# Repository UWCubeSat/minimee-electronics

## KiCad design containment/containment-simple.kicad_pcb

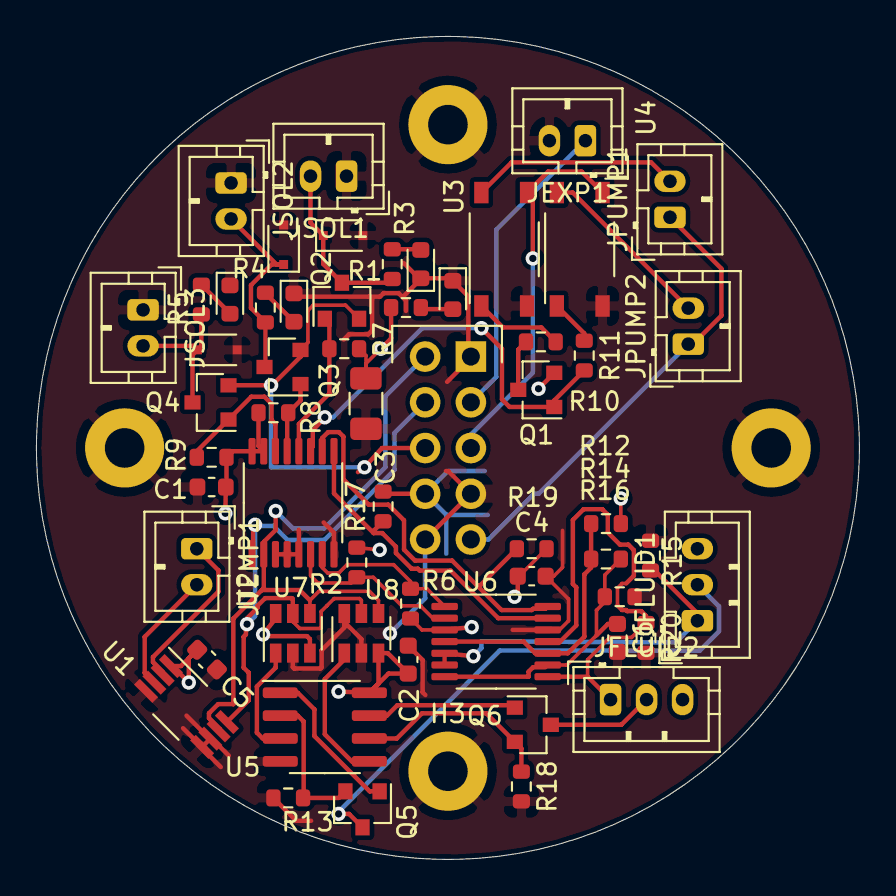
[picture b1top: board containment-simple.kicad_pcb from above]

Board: 2 copper layers, 45.7 x 45.7 mm, 61 parts (1 on the bottom side), 42 nets.

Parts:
C1, C2, C4, C5, C6: .1uF; C_0603_1608Metric
C3: 10uF; C_1206_3216Metric
D1, D5, D7, D9: LED; LED_0603_1608Metric
D4, D6, D8: D; D_SOD-323F
H1, H2, H3, H4: MountingHole_Pad; MountingHole_2-56_ExtraClearance
J1: Conn_02x05_Odd_Even; PinHeader_2x05_P2.54mm_Vertical
JEXP1: Conn_01x02; JST_PH_B2B-PH-K_1x02_P2.00mm_Vertical
JFLUID1, JFLUID2: Conn_01x03; JST_PH_B3B-PH-K_1x03_P2.00mm_Vertical
JPUMP1, JPUMP2: Conn_01x02; JST_PH_B2B-PH-K_1x02_P2.00mm_Vertical
JSOL1, JSOL2, JSOL3: Conn_01x02; JST_PH_B2B-PH-K_1x02_P2.00mm_Vertical
JTEMP1: Conn_01x02; JST_PH_B2B-PH-K_1x02_P2.00mm_Vertical
Q1, Q2, Q3, Q4: BSS84; SOT-23
Q5, Q6: BC846; SOT-23
R1, R3, R4, R5: 1k; R_0603_1608Metric
R2, R6, R7, R8, R9, R12, R14, R15, R16, R17, R19, R20: 10k; R_0603_1608Metric
R10, R11: 470; R_0603_1608Metric
R13, R18: 50; R_0603_1608Metric
U1: TMP411; VSSOP-8_3.0x3.0mm_P0.65mm
U2: PCA9557; TSSOP-16_4.4x5mm_P0.65mm
U3, U4: TLP175A; MFSOP6-4_4.4x3.6mm_P1.27mm
U5: LM358; SOIC-8_3.9x4.9mm_P1.27mm
U6: LM339; TSSOP-14_4.4x5mm_P0.65mm
U7, U8: MCP4725xxx-xCH; SOT-23-6

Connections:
+5V: C1.1, C2.1, C3.1, C4.1, C5.1, J1.8, JFLUID1.3, JFLUID2.3, Q1.2, R1.1, R2.1, R6.1, R7.1, R8.1, R9.1, R12.1, R17.1, R19.1, U1.1, U2.15, U2.16, U5.8, U6.3, U7.3, U7.6, U8.3
+12V: J1.6, Q2.2, Q3.2, Q4.2
/Fluid Sensors/1_3rds: C6.1, R14.2, R16.1, U6.7, U6.9
/Fluid Sensors/2_3rds: R12.2, R14.1, U6.4, U6.10
/HV+: J1.9, JPUMP1.1, JPUMP2.1
/HV-: J1.5, U3.4, U4.4
/experiment: J1.3, JEXP1.1
/p0: R2.2, U2.6, U6.2
/p1: R6.2, U2.7, U6.1
/p2: R17.2, U2.9, U6.13
/p3: R19.2, U2.10, U6.14
/p4: Q1.1, R11.2, U2.11
/p5: Q2.1, R7.2, U2.12
/p6: Q3.1, R8.2, U2.13
/p7: Q4.1, R9.2, U2.14
GND: C1.2, C2.2, C3.2, C4.2, C5.2, C6.2, D1.1, D4.2, D5.1, D6.2, D7.1, D8.2, D9.1, H1.1, H2.1, H3.1, H4.1, J1.1, J1.7, J1.10, JEXP1.2, JSOL1.1, JSOL2.1, JSOL3.1, R13.2, R15.2, R16.2, R18.2, R20.2, U1.4, U1.5, U1.6, U2.3, U2.4, U2.5, U2.8, U3.3, U4.3, U5.4, U6.12, U7.2, U8.2, U8.6
unnamed: D1.2, R1.2
unnamed: D4.1, JSOL1.2, Q2.3, R3.1
unnamed: D5.2, R3.2
unnamed: D6.1, JSOL2.2, Q3.3, R4.1
unnamed: D7.2, R4.2
unnamed: D8.1, JSOL3.2, Q4.3, R5.1
unnamed: D9.2, R5.2
unnamed: JFLUID1.1, R15.1, U6.5, U6.6
unnamed: JFLUID1.2, Q5.3
unnamed: JFLUID2.1, R20.1, U6.8, U6.11
unnamed: JFLUID2.2, Q6.3
unnamed: JPUMP1.2, U3.6
unnamed: JPUMP2.2, U4.6
unnamed: JTEMP1.1, U1.2
unnamed: JTEMP1.2, U1.3
unnamed: Q1.3, R10.2
unnamed: Q5.1, U5.1
unnamed: Q5.2, R13.1, U5.2
unnamed: Q6.1, U5.7
unnamed: Q6.2, R18.1, U5.6
unnamed: R10.1, U3.1
unnamed: R11.1, U4.1
unnamed: U5.3, U7.1
unnamed: U5.5, U8.1
scl: J1.4, U1.8, U2.1, U7.5, U8.5
sda: J1.2, U1.7, U2.2, U7.4, U8.4

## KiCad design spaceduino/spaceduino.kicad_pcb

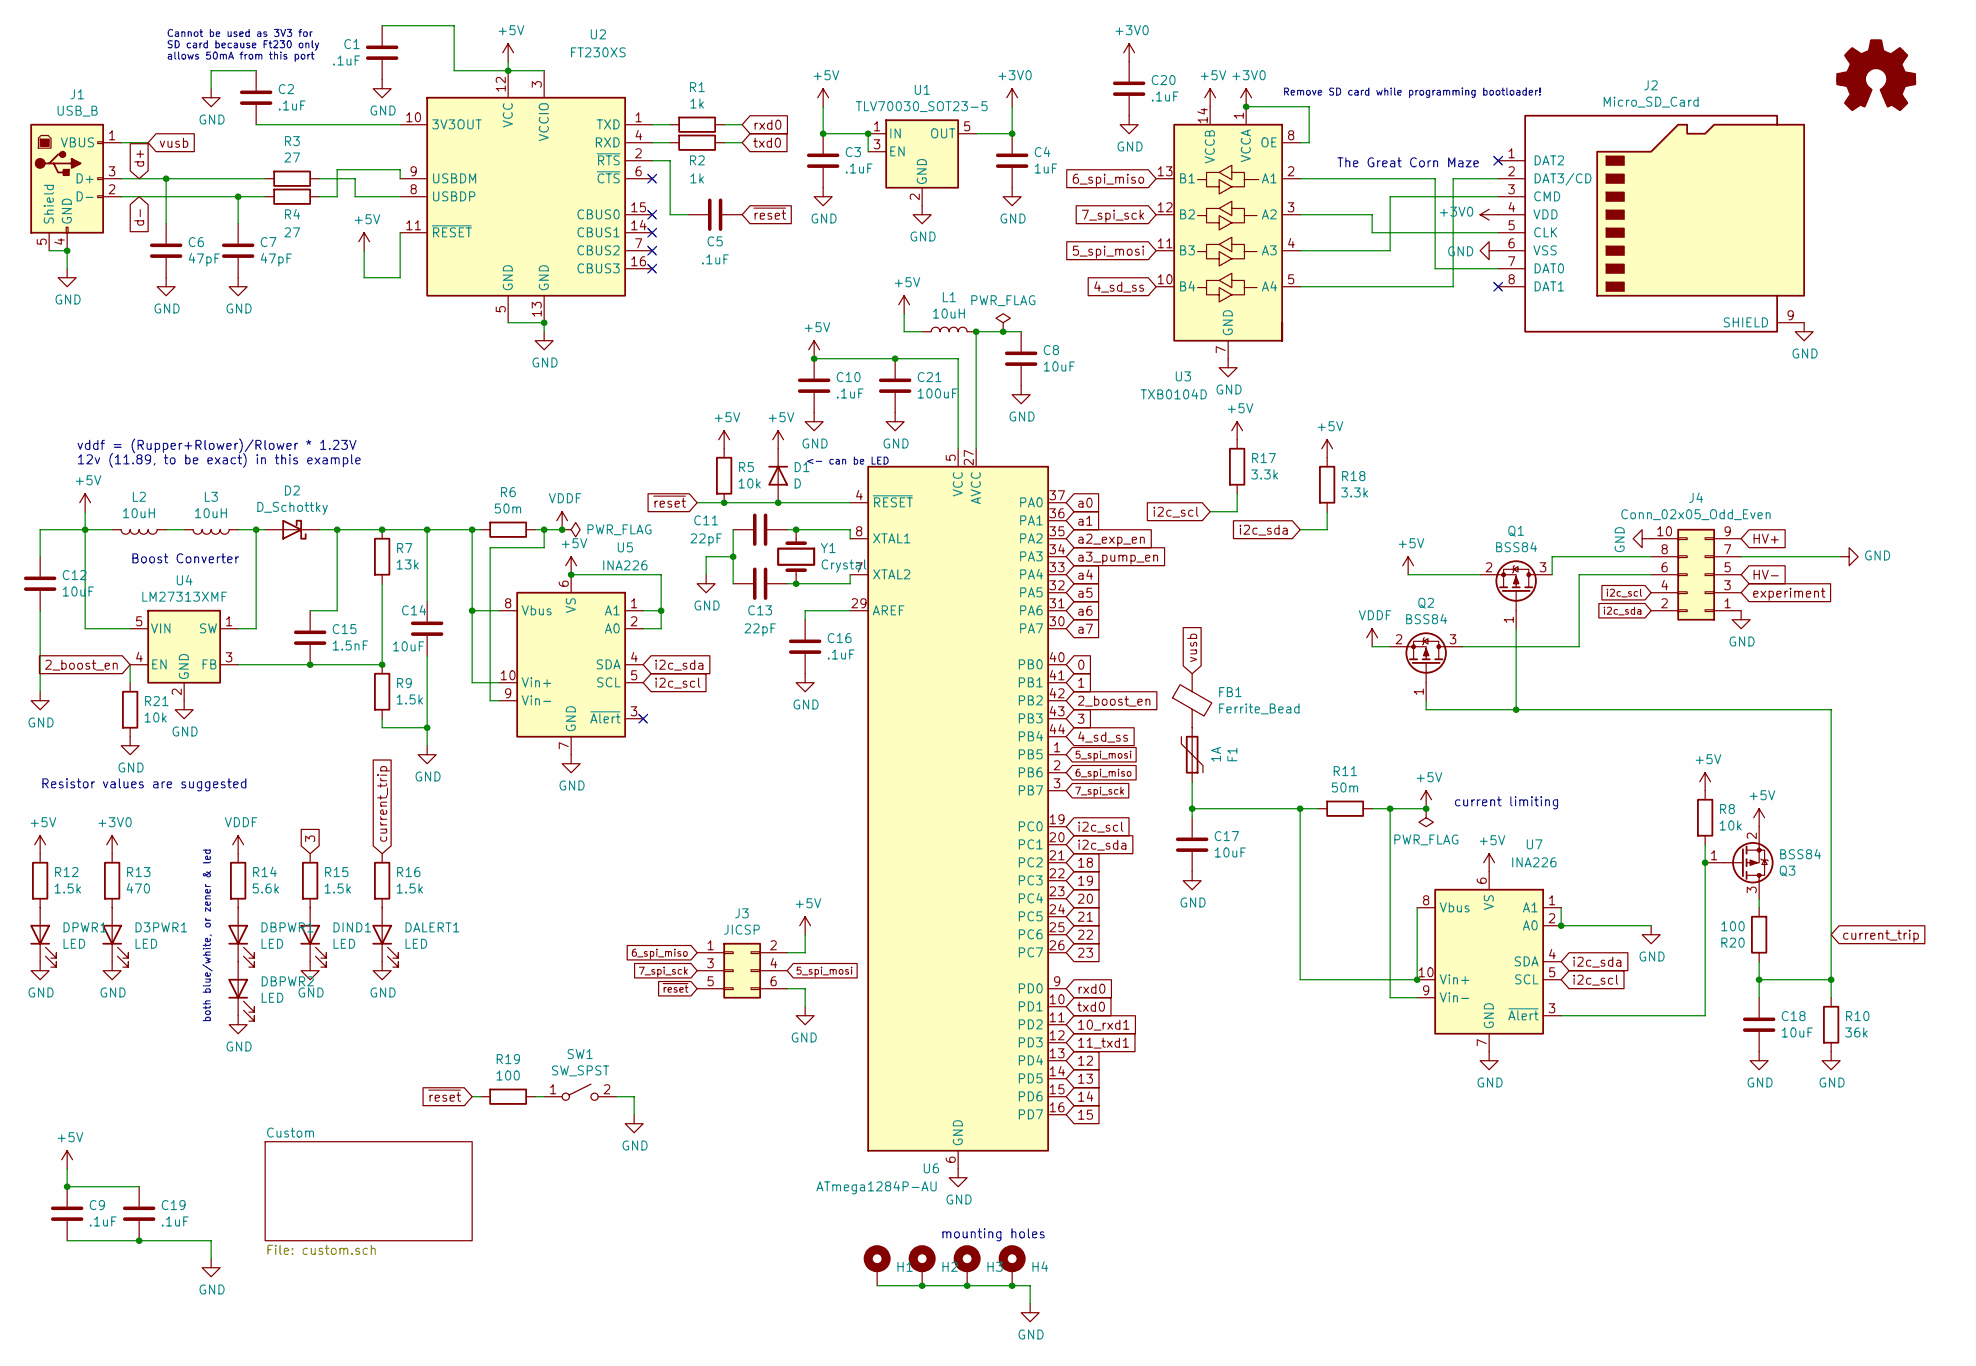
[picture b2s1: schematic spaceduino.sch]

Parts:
C1, C2, C3, C5, C9, C10, C16, C19, C20: .1uF; C_0603_1608Metric; LCSC C14663
C4: 1uF; C_1206_3216Metric; LCSC C1848
C6, C7: 47pF; C_0603_1608Metric; LCSC C1671
C8, C12, C14, C17, C18: 10uF; C_1206_3216Metric; LCSC C13585
C11, C13: 22pF; C_0603_1608Metric; LCSC C1653
C15: 1.5nF; C_0603_1608Metric; LCSC C1595
C21: 100uF; C_Radial_D5.0mm_H11.0mm_P2.00mm
D1: D; D_SOD-123; LCSC C8598
D2: D_Schottky; D_SOD-123; LCSC C8598
D3PWR1: LED; LED_0603_1608Metric; LCSC C72041
DALERT1: LED; LED_0603_1608Metric; LCSC C2286
DBPWR1, DBPWR2: LED; LED_0603_1608Metric; LCSC C72041
DIND1: LED; LED_0603_1608Metric; LCSC C72041
DPWR1: LED; LED_0603_1608Metric; LCSC C72041
F1: 1A; Fuse_1206_3216Metric; LCSC C315895
FB1: Ferrite_Bead; L_1206_3216Metric; LCSC C131463
H1, H2, H3, H4: MountingHole_Pad; MountingHole_2.2mm_M2_Pad
J1: USB_B; usb-type-b; Digikey 732-2734-ND
J2: Micro_SD_Card; HRS_DM3CS-SF
J3: JICSP; PinHeader_2x03_P2.54mm_Vertical
J4: Conn_02x05_Odd_Even; PinHeader_2x05_P2.54mm_Vertical
L1, L2, L3: 10uH; L_1210_3225Metric; LCSC C86073
LOGO1: Logo_Open_Hardware_Small; spaceduino-logo
Q1, Q2, Q3: BSS84; SOT-23; LCSC C10487
R1, R2: 1k; R_1206_3216Metric; LCSC C4410
R3, R4: 27; R_0603_1608Metric; LCSC C25190
R5, R8, R21: 10k; R_1206_3216Metric; LCSC C17902
R6, R11: 50m; R_1206_3216Metric; LCSC C201301
R7: 13k; R_0603_1608Metric; LCSC C22797
R9, R12, R15, R16: 1.5k; R_0603_1608Metric; LCSC C22843
R10: 36k; R_0603_1608Metric; LCSC C23147
R13: 470; R_1206_3216Metric; LCSC C17936
R14: 5.6k; R_0603_1608Metric; LCSC C23189
R17, R18: 3.3k; R_0603_1608Metric; LCSC C22978
R19, R20: 100; R_1206_3216Metric; LCSC C17901
SW1: SW_SPST; SolderJumper-2_P1.3mm_Open_TrianglePad1.0x1.5mm
U1: TLV70030_SOT23-5; SOT-23-5; Digikey 296-32412-1-ND
U2: FT230XS; SSOP-16_3.9x4.9mm_P0.635mm; Digikey 768-1135-1-ND
U3: TXB0104D; TSSOP-14_4.4x5mm_P0.65mm; Digikey 296-21928-1-ND
U4: LM27313XMF; SOT-23-5; LCSC C32355
U5, U7: INA226; VSSOP-10_3x3mm_P0.5mm; LCSC C49851
U6: ATmega1284P-AU; TQFP-44_10x10mm_P0.8mm; Digikey ATMEGA1284P-AURCT-ND
Y1: Crystal; Crystal_HC49-U_Vertical

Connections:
0: U6.40 (PB0)
1: U6.41 (PB1)
2_boost_en: R21.1, U4.4 (EN), U6.42 (PB2)
3: R15.1, U6.43 (PB3)
4_sd_ss: U3.10 (B4), U6.44 (PB4)
5_spi_mosi: J3.4, U3.11 (B3), U6.1 (PB5)
6_spi_miso: J3.1, U3.13 (B1), U6.2 (PB6)
7_spi_sck: J3.3, U3.12 (B2), U6.3 (PB7)
10_rxd1: U6.11 (PD2)
11_txd1: U6.12 (PD3)
12: U6.13 (PD4)
13: U6.14 (PD5)
14: U6.15 (PD6)
15: U6.16 (PD7)
18: U6.21 (PC2)
19: U6.22 (PC3)
20: U6.23 (PC4)
21: U6.24 (PC5)
22: U6.25 (PC6)
23: U6.26 (PC7)
+3V0: C4.1, C20.1, J2.4 (VDD), R13.1, U1.5 (OUT), U3.1 (VCCA), U3.8 (OE)
+5V: C1.1, C3.1, C9.1, C10.1, C12.1, C19.1, C21.1, D1.1 (K), J3.2, L1.1, L2.2, Q1.2 (S), Q3.2 (S), R5.1, R8.1, R11.1, R12.1, R17.1, R18.1, U1.1 (IN), U1.3 (EN), U2.3 (VCCIO), U2.11 (~RESET), U2.12 (VCC), U3.14 (VCCB), U4.5 (VIN), U5.1 (A1), U5.2 (A0), U5.6 (VS), U6.5 (VCC), U6.17 (VCC), U6.38 (VCC), U7.6 (VS), U7.9 (Vin-); also elsewhere on the board
GND: C1.2, C2.1, C3.2, C4.2, C6.2, C7.2, C8.2, C9.2, C10.2, C11.2, C12.2, C13.2, C14.2, C16.2, C17.2, C18.2, C19.2, C20.2, C21.2, D3PWR1.1 (K), DALERT1.1 (K), DBPWR2.1 (K), DIND1.1 (K), DPWR1.1 (K), H1.1, H2.1, H3.1, H4.1, J1.4 (GND), J1.5 (Shield), J2.6 (VSS), J2.9 (SHIELD), J3.6, J4.1, J4.7, J4.10, R9.2, R10.2, R21.2, SW1.2 (B), U1.2 (GND), U2.5 (GND), U2.13 (GND), U3.7 (GND), U4.2 (GND), U5.7 (GND), U6.6 (GND), U6.18 (GND), U6.28 (GND), U6.39 (GND), U7.1 (A1), U7.2 (A0), U7.7 (GND); also elsewhere on the board
HV+: J4.9; also elsewhere on the board
HV-: J4.5; also elsewhere on the board
unnamed: C2.2, U2.10 (3V3OUT)
unnamed: C5.2, U2.2 (~RTS)
unnamed: C8.1, L1.2, U6.27 (AVCC)
unnamed: C11.1, U6.8 (XTAL1), Y1.1
unnamed: C13.1, U6.7 (XTAL2), Y1.2
unnamed: C14.1, C15.1, D2.1 (K), R6.2, R7.1, U5.8 (Vbus), U5.10 (Vin+)
unnamed: C15.2, R7.2, R9.1, U4.3 (FB)
unnamed: C16.1, U6.29 (AREF)
unnamed: C17.1, F1.1, R11.2, U7.8 (Vbus), U7.10 (Vin+)
unnamed: D2.2 (A), L3.1, U4.1 (SW)
unnamed: D3PWR1.2 (A), R13.2
unnamed: DALERT1.2 (A), R16.2
unnamed: DBPWR1.1 (K), DBPWR2.2 (A)
unnamed: DBPWR1.2 (A), R14.2
unnamed: DIND1.2 (A), R15.2
unnamed: DPWR1.2 (A), R12.2
unnamed: F1.2, FB1.2
unnamed: J2.2 (DAT3/CD), U3.5 (A4)
unnamed: J2.3 (CMD), U3.4 (A3)
unnamed: J2.5 (CLK), U3.3 (A2)
unnamed: J2.7 (DAT0), U3.2 (A1)
unnamed: J4.6, Q2.3 (D)
unnamed: J4.8, Q1.3 (D)
unnamed: L2.1, L3.2
unnamed: Q3.1 (G), R8.2, U7.3 (~Alert~)
unnamed: Q3.3 (D), R20.2
unnamed: R1.2, U2.1 (TXD)
unnamed: R2.2, U2.4 (RXD)
unnamed: R3.1, U2.8 (USBDP)
unnamed: R4.1, U2.9 (USBDM)
unnamed: R19.1, SW1.1 (A)
VDDF: Q2.2 (S), R6.1, R14.1, U5.9 (Vin-)
a0: U6.37 (PA0)
a1: U6.36 (PA1)
a2_exp_en: U6.35 (PA2); also elsewhere on the board
a3_pump_en: U6.34 (PA3); also elsewhere on the board
a4: U6.33 (PA4)
a5: U6.32 (PA5)
a6: U6.31 (PA6)
a7: U6.30 (PA7)
current_trip: C18.1, Q1.1 (G), Q2.1 (G), R10.1, R16.1, R20.1
d+: C6.1, J1.3 (D+), R3.2
d-: C7.1, J1.2 (D-), R4.2
experiment: J4.3; also elsewhere on the board
i2c_scl: J4.4, R17.2, U5.5 (SCL), U6.19 (PC0), U7.5 (SCL); also elsewhere on the board
i2c_sda: J4.2, R18.2, U5.4 (SDA), U6.20 (PC1), U7.4 (SDA); also elsewhere on the board
rxd0: R1.1, U6.9 (PD0)
txd0: R2.1, U6.10 (PD1)
vusb: FB1.1, J1.1 (VBUS)
~reset: C5.1, D1.2 (A), J3.5, R5.2, R19.2, U6.4 (~RESET)

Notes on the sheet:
Boost Converter
The Great Corn Maze
Cannot be used as 3V3 for SD card because Ft230 only allows 50mA from this port
Remove SD card while programming bootloader!
vddf = (Rupper+Rlower)/Rlower * 1.23V 12v (11.89, to be exact) in this example
Resistor values are suggested
mounting holes
current limiting
<- can be LED
both blue/white, or zener & led

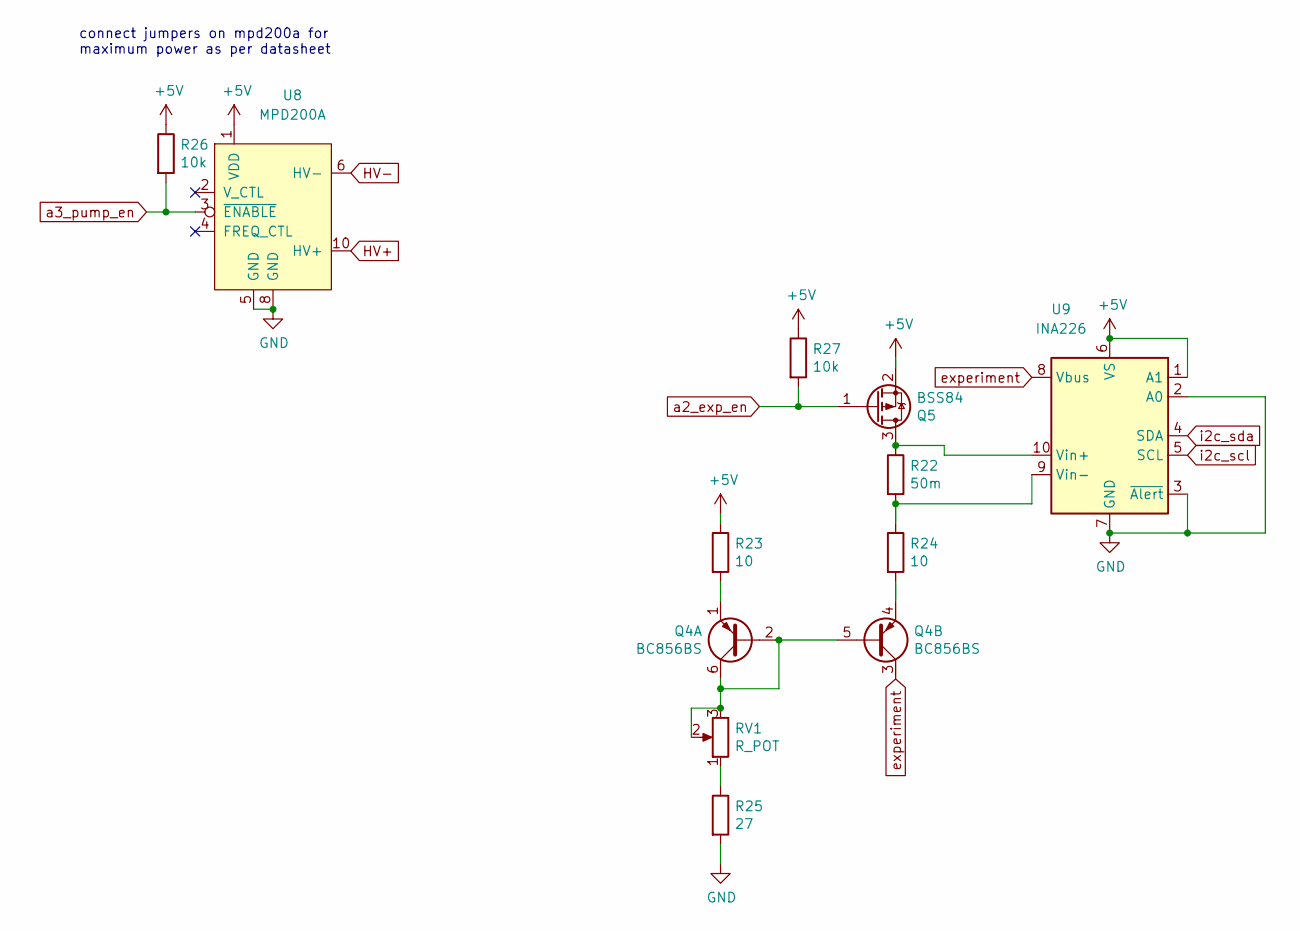
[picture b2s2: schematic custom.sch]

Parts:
Q4: BC856BS; SOT-363_SC-70-6; LCSC C105896
Q5: BSS84; SOT-23; LCSC C10487
R22: 50m; R_1206_3216Metric; LCSC C201301
R23, R24: 10; R_1206_3216Metric; LCSC C17903
R25: 27; R_0603_1608Metric; LCSC C25190
R26, R27: 10k; R_1206_3216Metric; LCSC C17902
RV1: R_POT; Potentiometer_Bourns_3296Y_Vertical
U8: MPD200A
U9: INA226; VSSOP-10_3x3mm_P0.5mm; LCSC C49851

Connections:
+5V: Q5.2 (S), R23.1, R26.1, R27.1, U8.1 (VDD), U9.1 (A1), U9.6 (VS); also elsewhere on the board
GND: R25.2, U8.5 (GND), U8.8 (GND), U9.2 (A0), U9.3 (~Alert~), U9.7 (GND); also elsewhere on the board
HV+: U8.10 (HV+); also elsewhere on the board
HV-: U8.6 (HV-); also elsewhere on the board
unnamed: Q4.1 (E1), R23.2
unnamed: Q4.2 (B1), Q4.5 (B2), Q4.6 (C1), RV1.2, RV1.3
unnamed: Q4.4 (E2), R24.2
unnamed: Q5.3 (D), R22.1, U9.10 (Vin+)
unnamed: R22.2, R24.1, U9.9 (Vin-)
unnamed: R25.1, RV1.1
a2_exp_en: Q5.1 (G), R27.2; also elsewhere on the board
a3_pump_en: R26.2, U8.3 (~ENABLE); also elsewhere on the board
experiment: Q4.3 (C2), U9.8 (Vbus); also elsewhere on the board
i2c_scl: U9.5 (SCL); also elsewhere on the board
i2c_sda: U9.4 (SDA); also elsewhere on the board

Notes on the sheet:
connect jumpers on mpd200a for maximum power as per datasheet

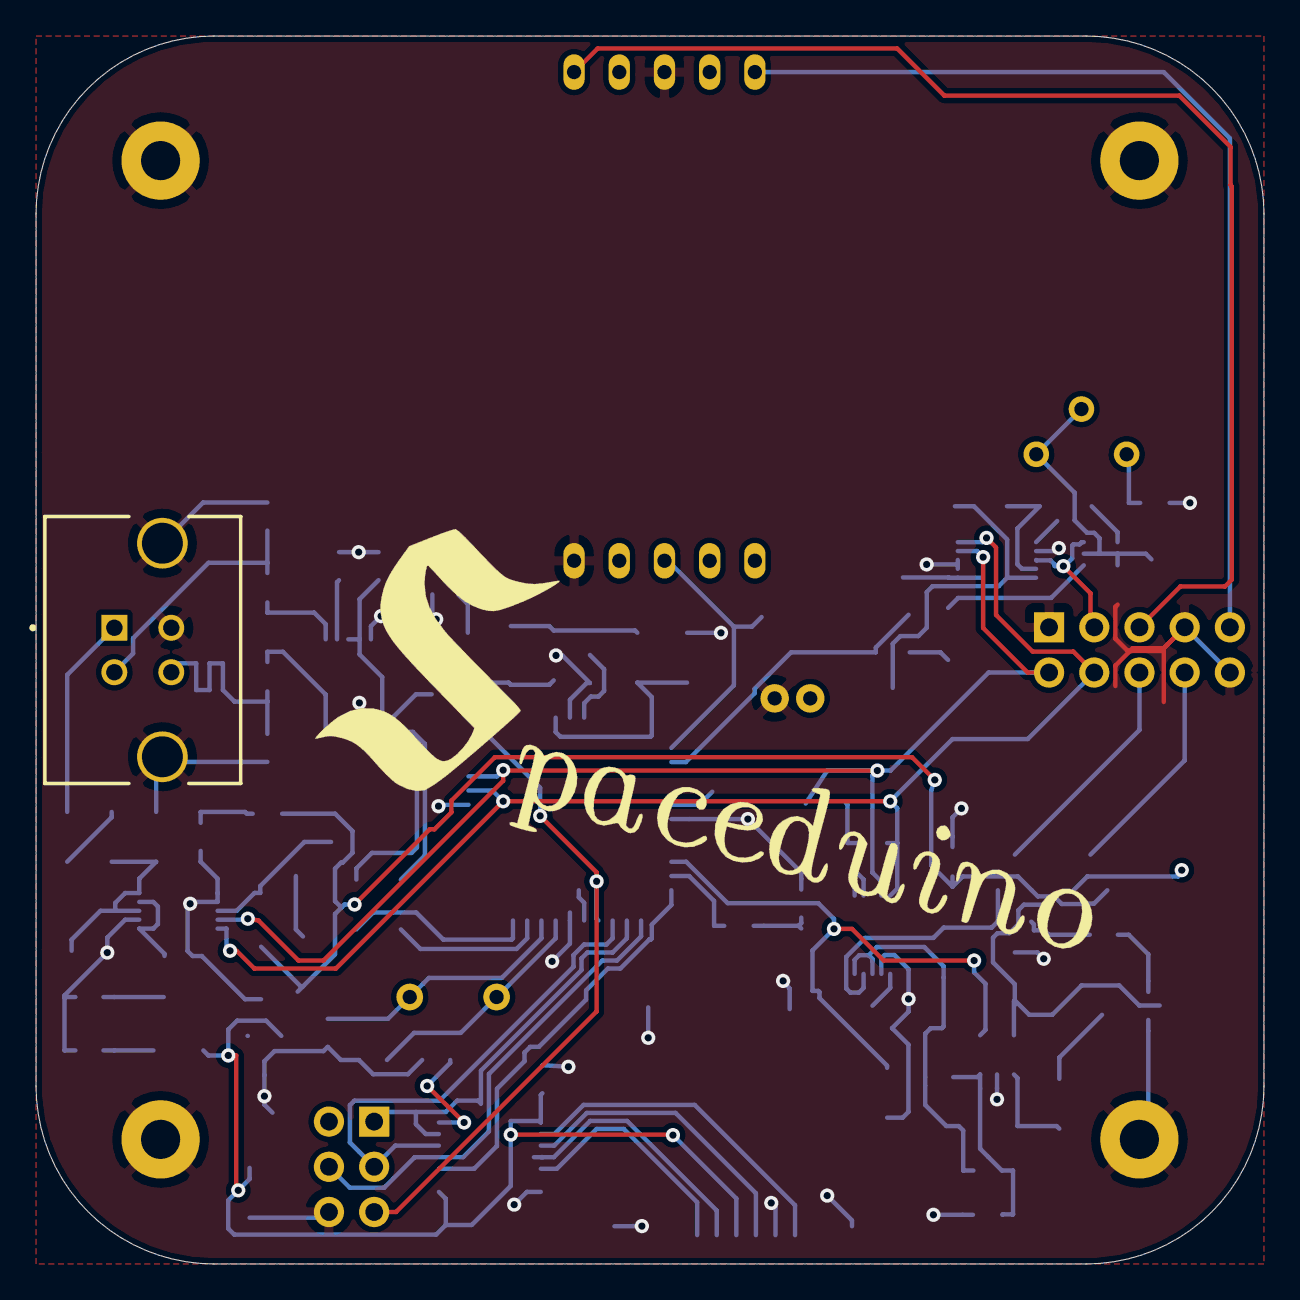
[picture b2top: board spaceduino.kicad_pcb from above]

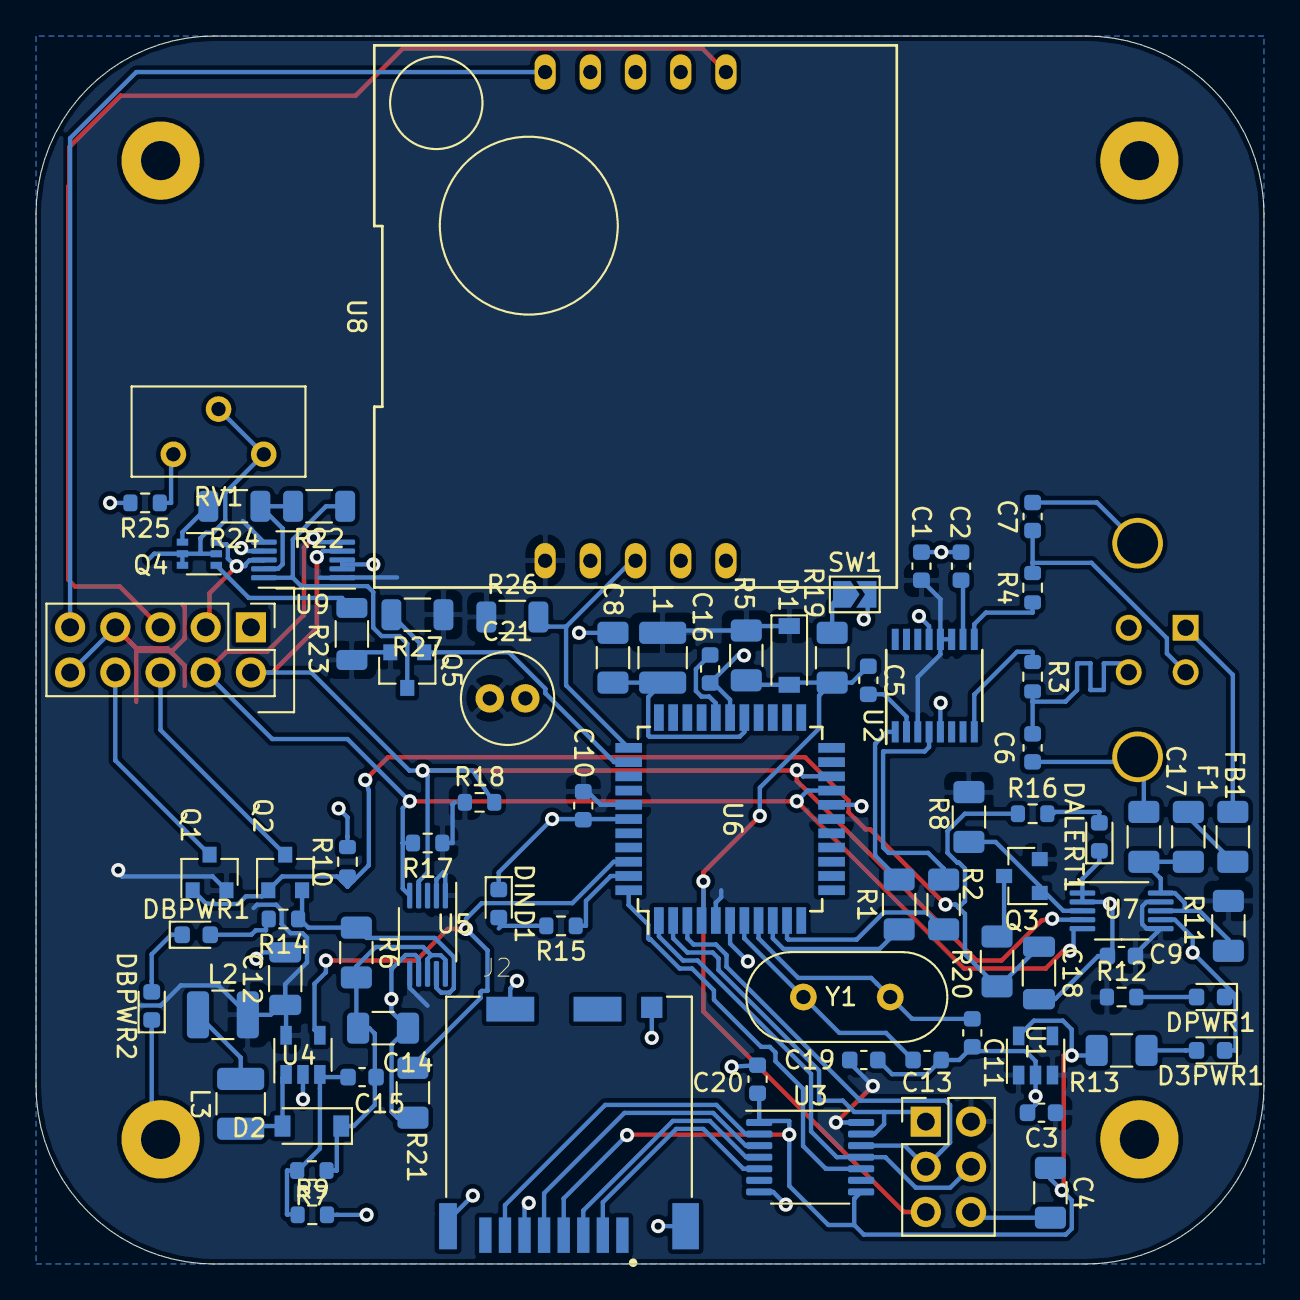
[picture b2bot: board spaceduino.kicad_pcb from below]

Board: 2 copper layers, 69.0 x 69.0 mm, 87 parts (81 on the bottom side), 61 nets.

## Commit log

2020-12-20 copied stuff from BONK
2020-12-21 add spixes
2020-12-21 spikey 2
2021-01-06 use the correct optocoupler
2021-01-06 add SD card footprint, PNP-based current mirror
2021-01-12 move more parts to jlcsmt catalog
2021-02-07 Added a BJT current mirror using BC846BDW1 NPN BJT's
2021-02-07 Filled some traces for Q4 and U6, need thicker power trace
2021-02-08 Added 500901-0801 Micro SD Socket (locking lid) to schematic, footprint and symbol library, removed current mirror
2021-02-09 Assigned footprints for SD Card, potentiometer, and resistors
2021-02-17 start fluid sensor
2021-03-15 inner containment baord lookin pretty good
2021-03-18 spaceduino laid out???
2021-03-19 use sd card that is actually in stock on digikey
2021-03-20 can i get a go dawgs
2021-04-05 ordered it supposedly
2021-06-10 containment schematic updated to include experiment & correct voltage on valve mosfets
